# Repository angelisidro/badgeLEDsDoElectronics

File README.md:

# Badge LED'sDoElectronics

Simple Badge diseñado con la herramienta EDA KiCad en uno de los talleres de la iniciativa LED´sDoElectronicsGt, esta pequeña tarjeta contiene un circuito oscilador.

# ¿Donde puedo ver la sesión?

La sesión se realizo por medio de un facebook live en la cuenta de LEDsDoElectronics, pero lo puedes encontrar en mi [Canal de youtube][YTB].

[YTB]: https://youtu.be/NXX7O06I9Ms

# Lista de materiales

- KiCad Instalado 
- LED rojos X 3 
- Transistores 2N3904 X 2
- Resistores 470 ohms x 3 
- Capacitores 10uF x 2
- Resistores 100K ohms x 2 
- Fuente de alimentación 5v a 9v

# Licencia

Hardware License: CERN OHL v1.0 para más información visitar el siguiente [Link][CERN_v1].

[CERN_v1]: https://ohwr.org/project/cernohl/wikis/Documents/CERN-OHL-version-1.2

Software License: None

Documentation License: CC BY 4.0 International

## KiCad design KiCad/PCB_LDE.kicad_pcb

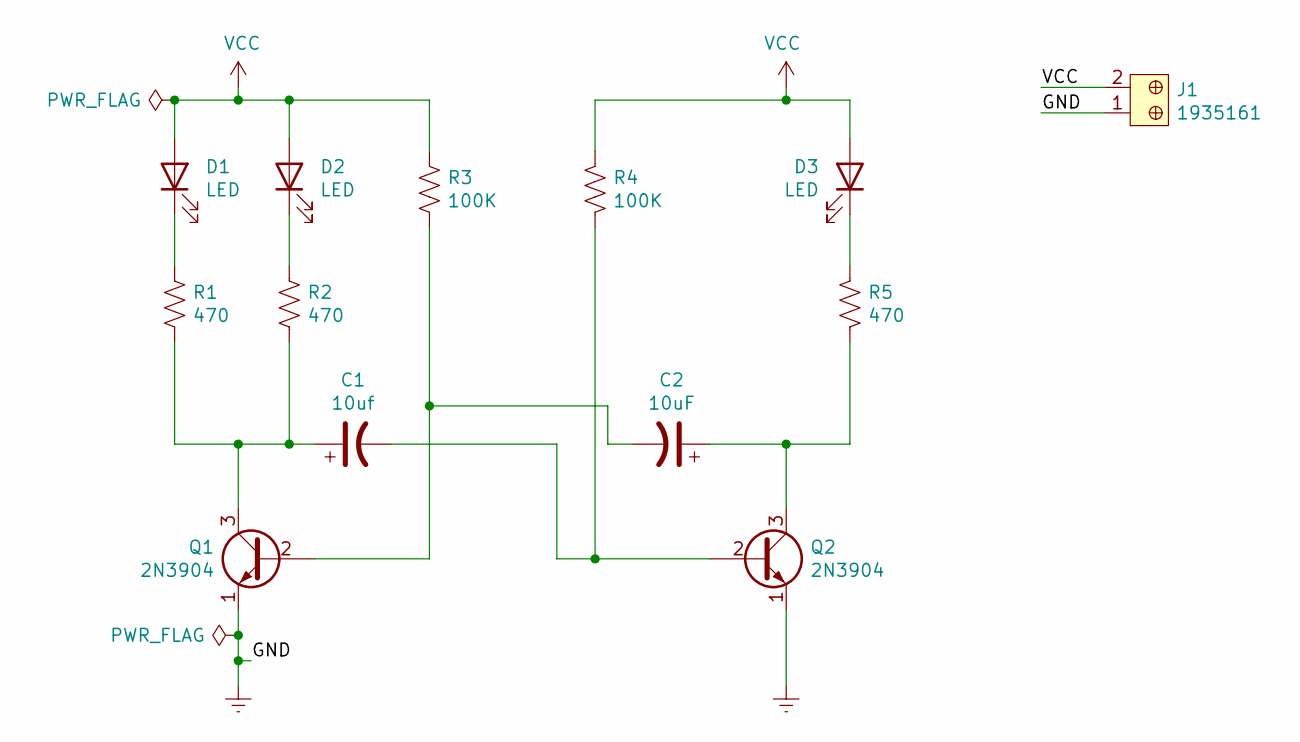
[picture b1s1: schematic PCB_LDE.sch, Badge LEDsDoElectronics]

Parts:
C1: 10uf; CP_Radial_D5.0mm_P2.50mm
C2: 10uF; CP_Radial_D5.0mm_P2.50mm
D1, D2, D3: LED; LED_D5.0mm
J1: 1935161; TerminalBlock_Altech_AK300-2_P5.00mm; MPN 1935161; Digi-Key_PN 277-1667-ND
Q1, Q2: 2N3904; TO-92_Inline
R1, R2, R5: 470; R_Axial_DIN0207_L6.3mm_D2.5mm_P7.62mm_Horizontal
R3, R4: 100K; R_Axial_DIN0207_L6.3mm_D2.5mm_P7.62mm_Horizontal

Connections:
Earth: J1.1, Q1.1 (E), Q2.1 (E)
unnamed: C1.1, Q1.3 (C), R1.2, R2.2
unnamed: C1.2, Q2.2 (B), R4.2
unnamed: C2.1, Q2.3 (C), R5.2
unnamed: C2.2, Q1.2 (B), R3.2
unnamed: D1.1 (K), R1.1
unnamed: D2.1 (K), R2.1
unnamed: D3.1 (K), R5.1
VCC: D1.2 (A), D2.2 (A), D3.2 (A), J1.2, R3.1, R4.1

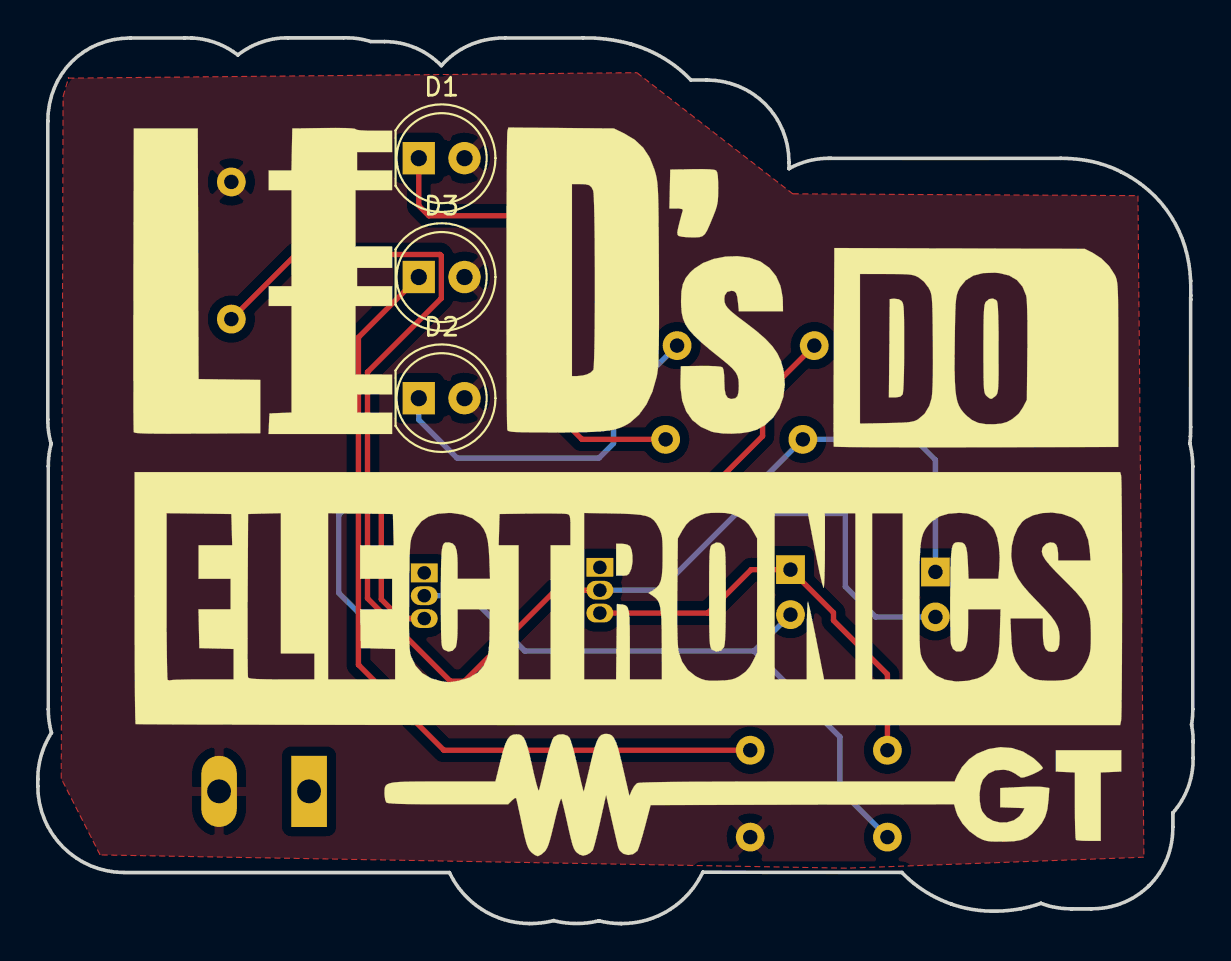
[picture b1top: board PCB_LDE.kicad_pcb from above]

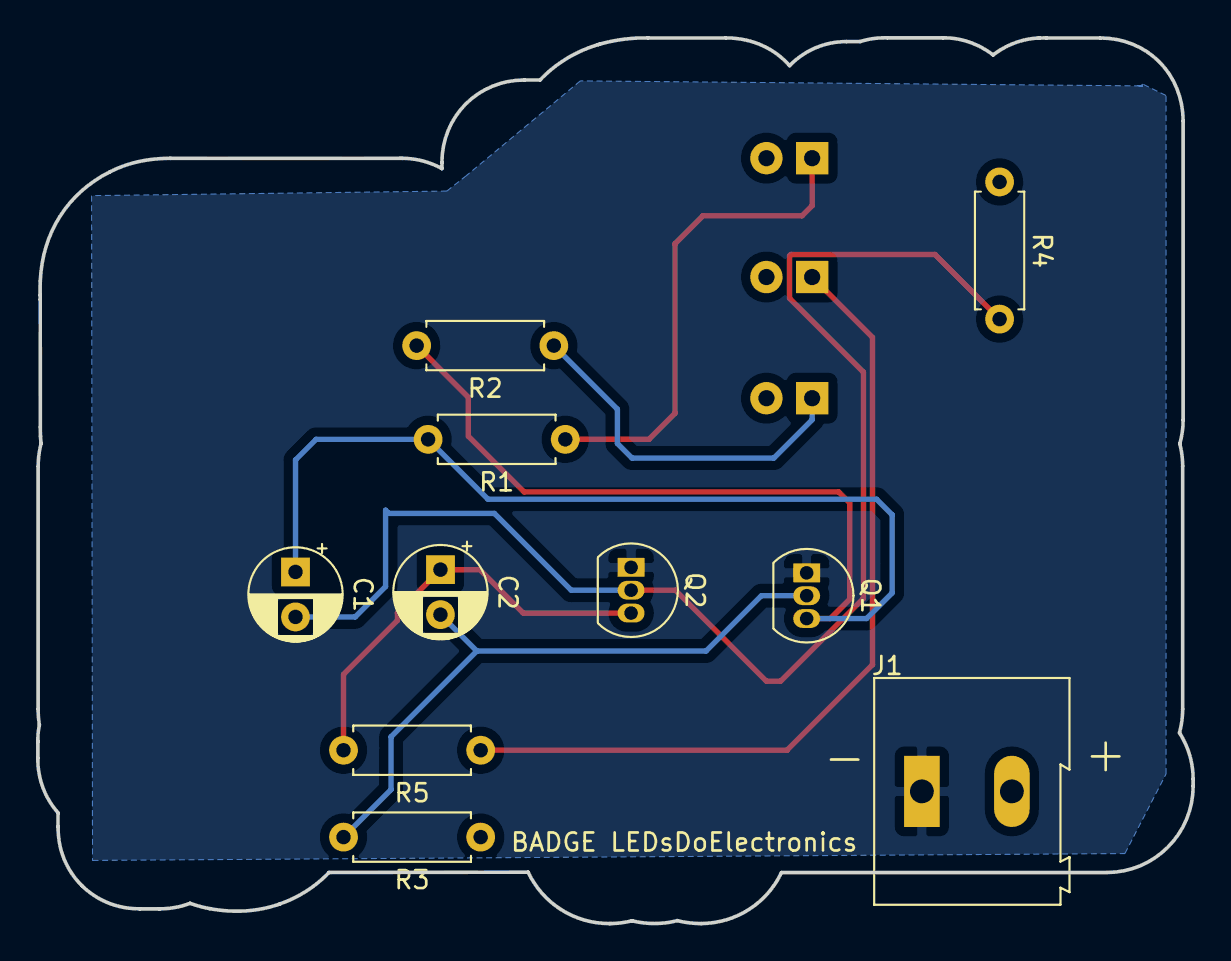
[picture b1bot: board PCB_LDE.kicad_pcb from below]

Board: 2 copper layers, 64.2 x 49.2 mm, 13 parts (10 on the bottom side), 9 nets.
